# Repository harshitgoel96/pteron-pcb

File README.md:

# Pteron36 Split Keyboard
## Intro 

This project is the split evolution of the [pteron-pcb](https://github.com/Kraken-Jokes/pteron-pcb) project, which itself is the evolution of the [Pteron-Keyboard](https://github.com/FSund/pteron-keyboard) project, an incredible ergonomic keyboard that was handwired only.

The keyboard is being desinged to be used with [Miryoku-layout](https://github.com/manna-harbour/miryoku), this layout out aims to have efficient use of split keyboard.

NOTE: The keyboard design has reached its goal, I will not be doing any more development on this board. The support will still be provided. Any issues found by community will be addressed.
NOTE: Update Jan 4th, 2023, a few people have reached out to me with intentions to use the 38key version of the keyboard. The firmware changes have not been merged with QMK mainline yet. For the timebeing, please use this [forked branch to use 38key firmware](https://github.com/harshitgoel96/qmk_firmware/tree/pteron36_38/keyboards/pteron36). I will be working to update the firmware and merge it into the mainline.

#### BOM
| Component           | part number                             | QTY | Comment                            |
| ------------------- | --------------------------------------- | --- | ---------------------------------- |
| PCB                 | Gerber in release section               | 2   |                                    |
| Diode               | 1n4148, SOD123 for smd, or Through hole | 38/36/34  |                                    |
| ProMicro/Bluemicro  |                                         | 2   | Firmwaree not merged with QMK/ZMK, reach out to me on how to build the firmware  |
| TRRS Jack           | PJ-320A                                 | 2   |                                    |
| Switches            | Cherry, Alps, Choc                      | 38/36/34  | check PCB compatibility section for more infromation |
| Keycaps             | your choice                             | 38/36/34  |                                    |
| TRRS Cable | TRRS cables have 3 black rings, make sure to check the number | 1   |                                    |

#### BOM for optional components
| Component           | part number                             | QTY | Comment                            |
| ------------------- | --------------------------------------- | --- | ---------------------------------- |
| Mini tactile switch | PTS526 SMG15 SMTR2 LFS                  | 2   | You can use tweasers to Reset promicro      |
| Rotary Encoder      | EC11                                    | 2   | QMK, VIAL ✔️ ZMK 🚧 |
| OLED | 128x32 SSD1306 I2C                  | 2   | QMK, VIAL ✔️ ZMK 🚧 |

## Built keyboard

## Build guide
Build guide is added in BUILD.md file.

## Firmware file
Pteron36 has been merged into QMK master with support for miryoku and via. VIA config in available in release section.
Pteron36 has been merged into VIAL QMK fork. 

## Important
The PCB and the case have been tested with MX Switches. 

### PCB compatibility matrix
| PCB version | MX Support | Alps Support | Choc support | Remark |
|-------------|------------|--------------|--------------|--------------|
| V1.1.0 | :heavy_check_mark: |:heavy_check_mark: | :x: | |
| V1.2.0 | :heavy_check_mark: |:heavy_check_mark: | :heavy_check_mark: | |
| V1.3.0 | :heavy_check_mark: |:heavy_check_mark: | :heavy_check_mark: | Cleaner trace routing, added mounting holes |
| V1.4.0 | :heavy_check_mark: |:heavy_check_mark: | :heavy_check_mark: | Replaced sharp angle with curves, more cleaner pcb look |
To use choc switches, make sure to use V1.2.0 files from release section.

### Case compatibility

| Case Type | MX Support | Alps Support | Choc support |
|-------------|------------|--------------|--------------|
| Acrylic | :heavy_check_mark: |:x: | :exclamation: Untested, plate need to be lasered on 2mm sheet |
| 3D Printed | 	:construction: Design complete, testing first prototypes |:x: | 	:construction: Design complete, testing first prototypes |

Tenting support added, need M4 screws for tenting holes.
### Acrylic Case assembly
Keyboard supports both ProMicro, and nrf52840 based Bluetooth promicro (bluemicro,nice!nano, etc). The case height will be different to accomodate batteries.
The case designed to be done 3mm acrylic.
Screw M2 6mm 36 nos
Standoff HEX M2 6mm or 9mm 18 nos

For tenting you need.
4x M4 25mm-30mm screws.
4x M4 15mm screws.
8x M4 dome nuts for screw bottom.
8x M4 nut for holding case at required height.
#### Case config for ProMicro
All 4 files need to be cut twice so total 8 pieces. 4 per half.
Screw and standoff needs to be M2. Standoff lenght will be 6mm. Screw length will be 5-6mm. 

#### Case config for Bluemicro, Nine!nano
The case will be taller by 3mm to accomodate battery. This is assuming battery battery thickness is between 3mm - 4mm. For thickerbattery add close layer and standoff length as required.
Close.dfx will be cut 4 times, rest all 3 files need to be cut twice so total 10 pieces. 5 per half.
Screw and standoff needs to be M2. Standoff lenght will be 9mm. Screw length will be 5-6mm.

## ToDo List (In order or priority)
* Add build guide. :construction:
* OLED Support in ZMK  :construction:. OLED working in QMK now  :heavy_check_mark: 
* Encoder Support in ZMK  :construction:. Encoder working in QMK now  :heavy_check_mark: 
* Get firmware merged and ZMK.

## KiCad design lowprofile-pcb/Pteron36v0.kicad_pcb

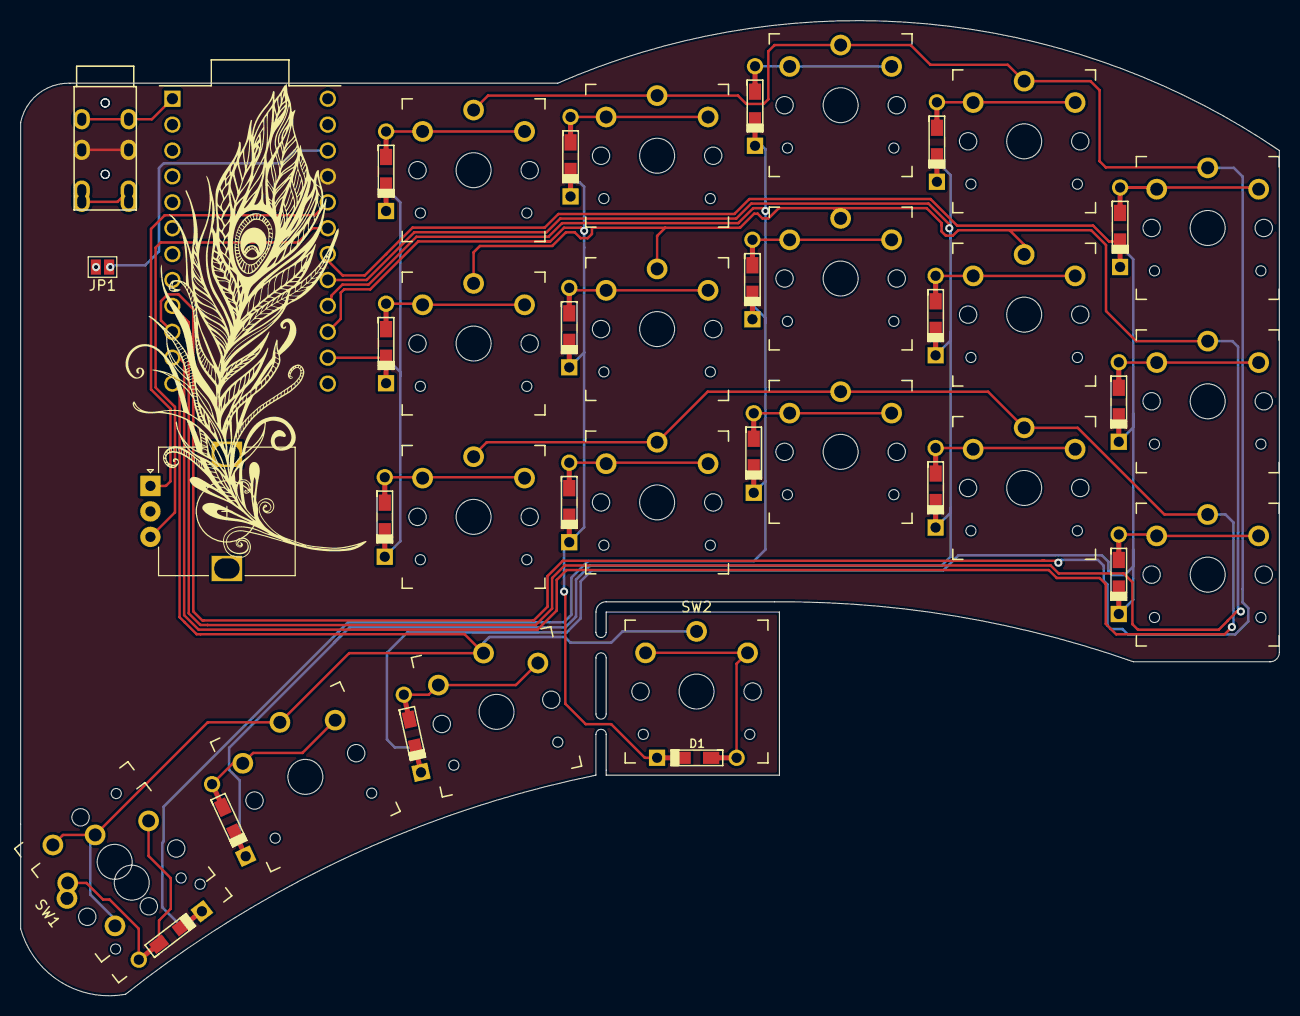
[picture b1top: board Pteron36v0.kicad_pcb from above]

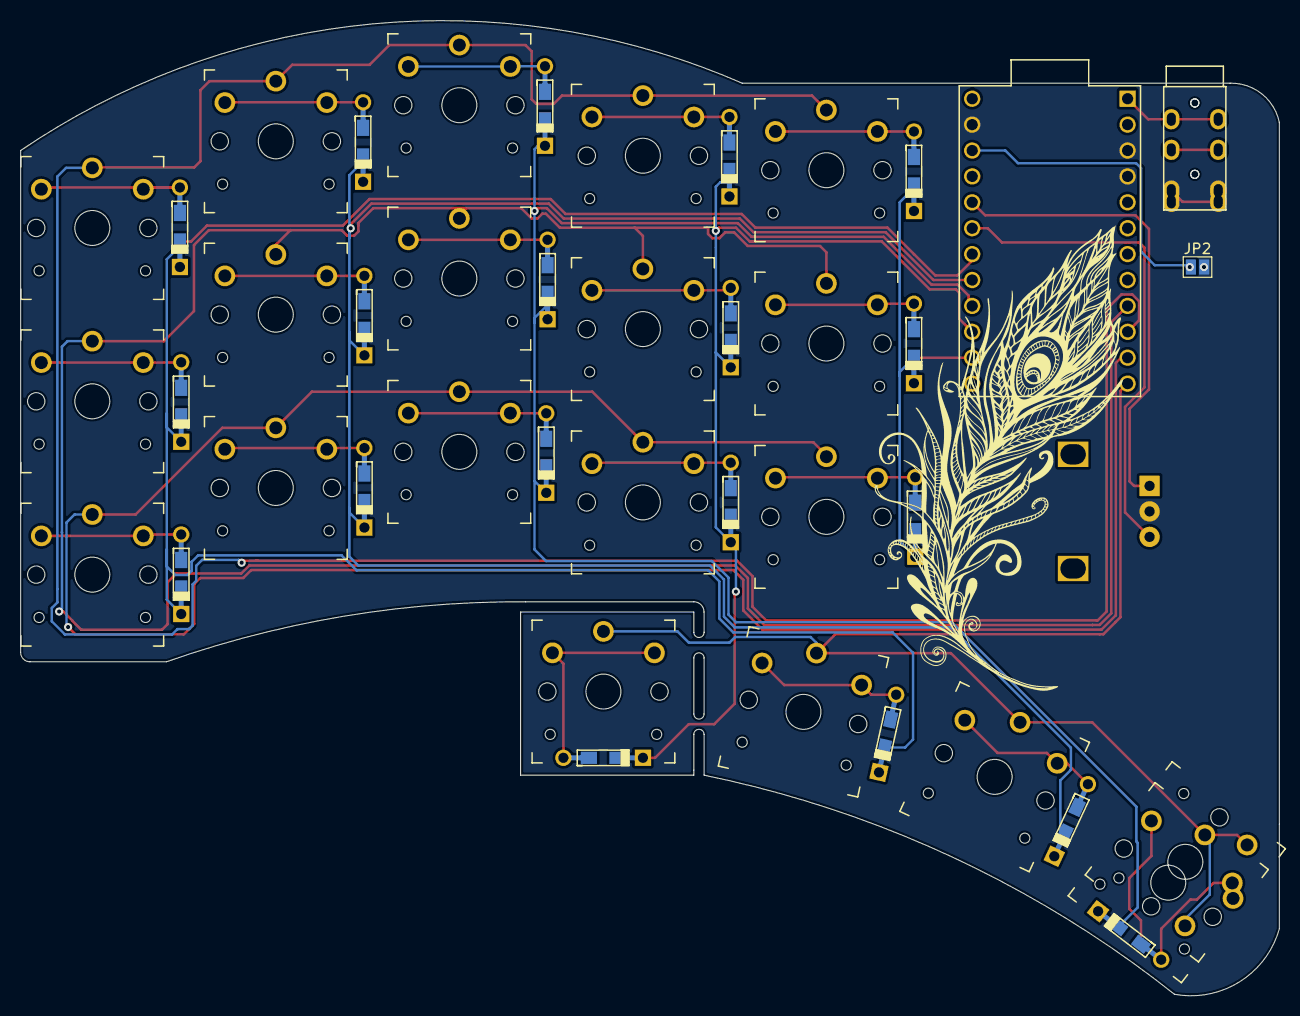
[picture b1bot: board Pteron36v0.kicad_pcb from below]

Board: 2 copper layers, 123.5 x 95.6 mm, 47 parts (3 on the bottom side), 34 nets.

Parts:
D1, D7, D8, D9, D10, D12, D13, D14, D15, D17, D18, D19, D20, D22, D23, D24, D26, D27, D28: 1N4148; Diode-dual
EN_1: Rotary_Encoder; RotaryEncoder_Alps_EC12E_Vertical_H20mm
J1, J2: AudioJack4; TRRS-PJ-320A
JP1, JP2: JUMPER-PAD-2-NO; SolderJumper-2_P1.3mm_Open_Pad1.0x1.5mm
LOGO3, LOGO4: LOGO-OTL; peacock-medium
SW1, SW2, SW7, SW8, SW9, SW10, SW12, SW13, SW14, SW15, SW17, SW18, SW19, SW20, SW22, SW23, SW24, SW26, SW27, SW28: SW_PUSH; PG1350_reversible
U1: ProMicro

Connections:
/Col1: D7.1 (K), D8.1 (K), D9.1 (K), D10.1 (K), U1.18 (F6)
/Col2: D12.1 (K), D13.1 (K), D14.1 (K), D15.1 (K), U1.17 (F7)
/Col3: D17.1 (K), D18.1 (K), D19.1 (K), D20.1 (K), U1.16 (B1)
/Col4: D1.1 (K), D22.1 (K), D23.1 (K), D24.1 (K), U1.15 (B3)
/Col5: D26.1 (K), D27.1 (K), D28.1 (K), U1.14 (B2)
/RotA: EN_1.A, U1.20 (F4)
/RotB: EN_1.B, U1.19 (F5)
/Row1: SW7.1, SW12.1, SW17.1, SW22.1, SW26.1, U1.10 (E6)
/Row2: SW8.1, SW13.1, SW18.1, SW23.1, SW27.1, U1.9 (D7)
/Row3: SW9.1, SW14.1, SW19.1, SW24.1, SW28.1, U1.11 (B4)
/Row4: SW1.1, SW2.1, SW10.1, SW15.1, SW20.1, U1.12 (B5)
/Serial: J1.4, J2.4, U1.1 (TX)
GND: EN_1.C, J1.1, J1.2, J2.1, J2.2, JP1.2, JP2.2, U1.3 (GND), U1.4 (GND), U1.23 (GND)
unnamed: D1.2 (A), SW2.2
unnamed: D7.2 (A), SW7.2
unnamed: D8.2 (A), SW8.2
unnamed: D9.2 (A), SW9.2
unnamed: D10.2 (A), SW10.2
unnamed: D12.2 (A), SW12.2
unnamed: D13.2 (A), SW13.2
unnamed: D14.2 (A), SW14.2
unnamed: D15.2 (A), SW15.2
unnamed: D17.2 (A), SW17.2
unnamed: D18.2 (A), SW18.2
unnamed: D19.2 (A), SW19.2
unnamed: D20.2 (A), SW1.2, SW20.2
unnamed: D22.2 (A), SW22.2
unnamed: D23.2 (A), SW23.2
unnamed: D24.2 (A), SW24.2
unnamed: D26.2 (A), SW26.2
unnamed: D27.2 (A), SW27.2
unnamed: D28.2 (A), SW28.2
unnamed: JP1.1, JP2.1, U1.22 (RST)
VCC: J1.3, J2.3, U1.21 (VCC)

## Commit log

2021-04-12 add split wiring for standard Pteron56v0
2021-04-12 split36 version
2021-04-12 finalised the design, add mounting holes
2021-04-12 small improvements
2021-04-12 added gerber files
2021-04-13 remove top row.
2021-04-13 simplified wiring, lily58 like pro micro placement
2021-04-13 made small changes for mounting holes
2021-04-13 added top and bottom gerber
2021-04-13 finished rev1 for pteron36
2021-04-13 Updated License
2021-04-13 added images, added project info
2021-04-13 remove firmware, updated read.md
2021-04-14 fix incorrect link for OG Pteron
2021-04-14 added oled support
2021-04-14 added oled, clean silkscreen
2021-04-15 add oled, pwm pad, reset switch, moved trrs closer to top, to get simpler casefiles
2021-04-15 add renders
2021-04-16 rename files to pteron36, to reflect correct keysize. add logo and text
2021-04-17 add encoder, cleanup files, rename files.
2021-04-17 update gerber and image files
2021-04-17 udpate change log
2021-04-25 added choc and mx support in single pcb.
2021-04-25 added acrylic layer case details
2021-05-12 updated pcb
2021-05-12 cache update
2021-05-12 update renders
2021-05-12 added prototyp pcb image
2021-05-13 add known issue about choc switch in main branch
2021-05-13 cache updatef'
2021-05-19 add BOM
2021-05-19 add oled in BOM
2021-05-19 separte section for optional components
2021-05-19 add finished image
2021-05-19 cleaning readme
2021-05-23 update hole size for standoff
2021-06-18 updated case
2021-06-21 update image
2021-06-21 update version information in readme
2021-06-21 add case info
2021-06-21 update some more info
2021-06-21 add to do list
2021-06-21 add case files
2021-06-21 add release files
2021-06-22 add 3d case file for choc switch with tenting
2021-06-23 add case assembly detail
2021-06-23 build instruction
2021-06-23 add build guide
2021-06-25 update 3d case files
2021-06-25 add acrylic case with tent holes
2021-06-25 updated case info in readme
2021-06-26 update case file for better diode clearance, some chamfer, and countersunk
2021-06-27 add via, and vial firmware
2021-06-27 added firmware info in readme
2021-06-30 add changes to base. thicken pcb post, better tenting support.
2021-07-06 use crkbd footprint for better manufacturing
2021-07-07 update footprint for better support from manuf
2021-07-07 Update README.md
    update readme
2021-07-07 reroute pcb, just for kicks
2021-07-07 push tenting case
2021-07-10 final pcb
2021-07-10 generate final gerber
2021-07-10 final info added in readme
2021-07-10 update final pcb images and gerber
2021-07-10 update case files
2021-07-12 clean up pads
2021-07-12 update pcb render
2021-07-14 keebio footprint
2021-07-22 rename folder for better separation between original and lowprofile pcb
2021-07-22 rename folder
2021-07-25 separate pcb for mx-alps only
2021-07-25 add separate pcb for mx alps
2021-07-28 i might have buggered it
    this is mine
2021-07-28 a
    a
2021-07-28 cleaner tracing
2021-07-28 updated board outline and wiring
2021-07-28 regen gerber LP
2021-07-28 update gerber zip
2021-07-28 update outline with curves, cleaup wiring
2021-07-28 update universal pcb with curvy layout
2021-07-28 update wiring for lowprofile
2021-07-28 parking changes temp
2021-07-28 finalise art and board
2021-07-28 finalize low profile pcb
2021-07-28 ready for multi slot version of pcb
2021-07-28 updaate pcb
2021-07-28 eureka of super finish
2021-07-28 super is ready
2021-07-28 verify gerber
2021-08-06 introduce the snapable pcb with 4 config of keyboard possible
2021-08-18 update bom qtr for trrs cable
2021-08-18 almost ready final super pcb
2021-09-25 add stl for 38 key variant case, add 1.5 u on lowprofile keyboard
2021-12-25 updated image render to latest version of the pcb
2022-01-17 major changes in pcb, choc support removed from universal pcb, and made mx/alps only, this is because a choc spec lowprofile pcb exists. no more need for universal pcb
2022-01-17 update render images
2022-01-17 add 4-th key in thumb for removable config
2024-01-04 update info about 38key firmware
